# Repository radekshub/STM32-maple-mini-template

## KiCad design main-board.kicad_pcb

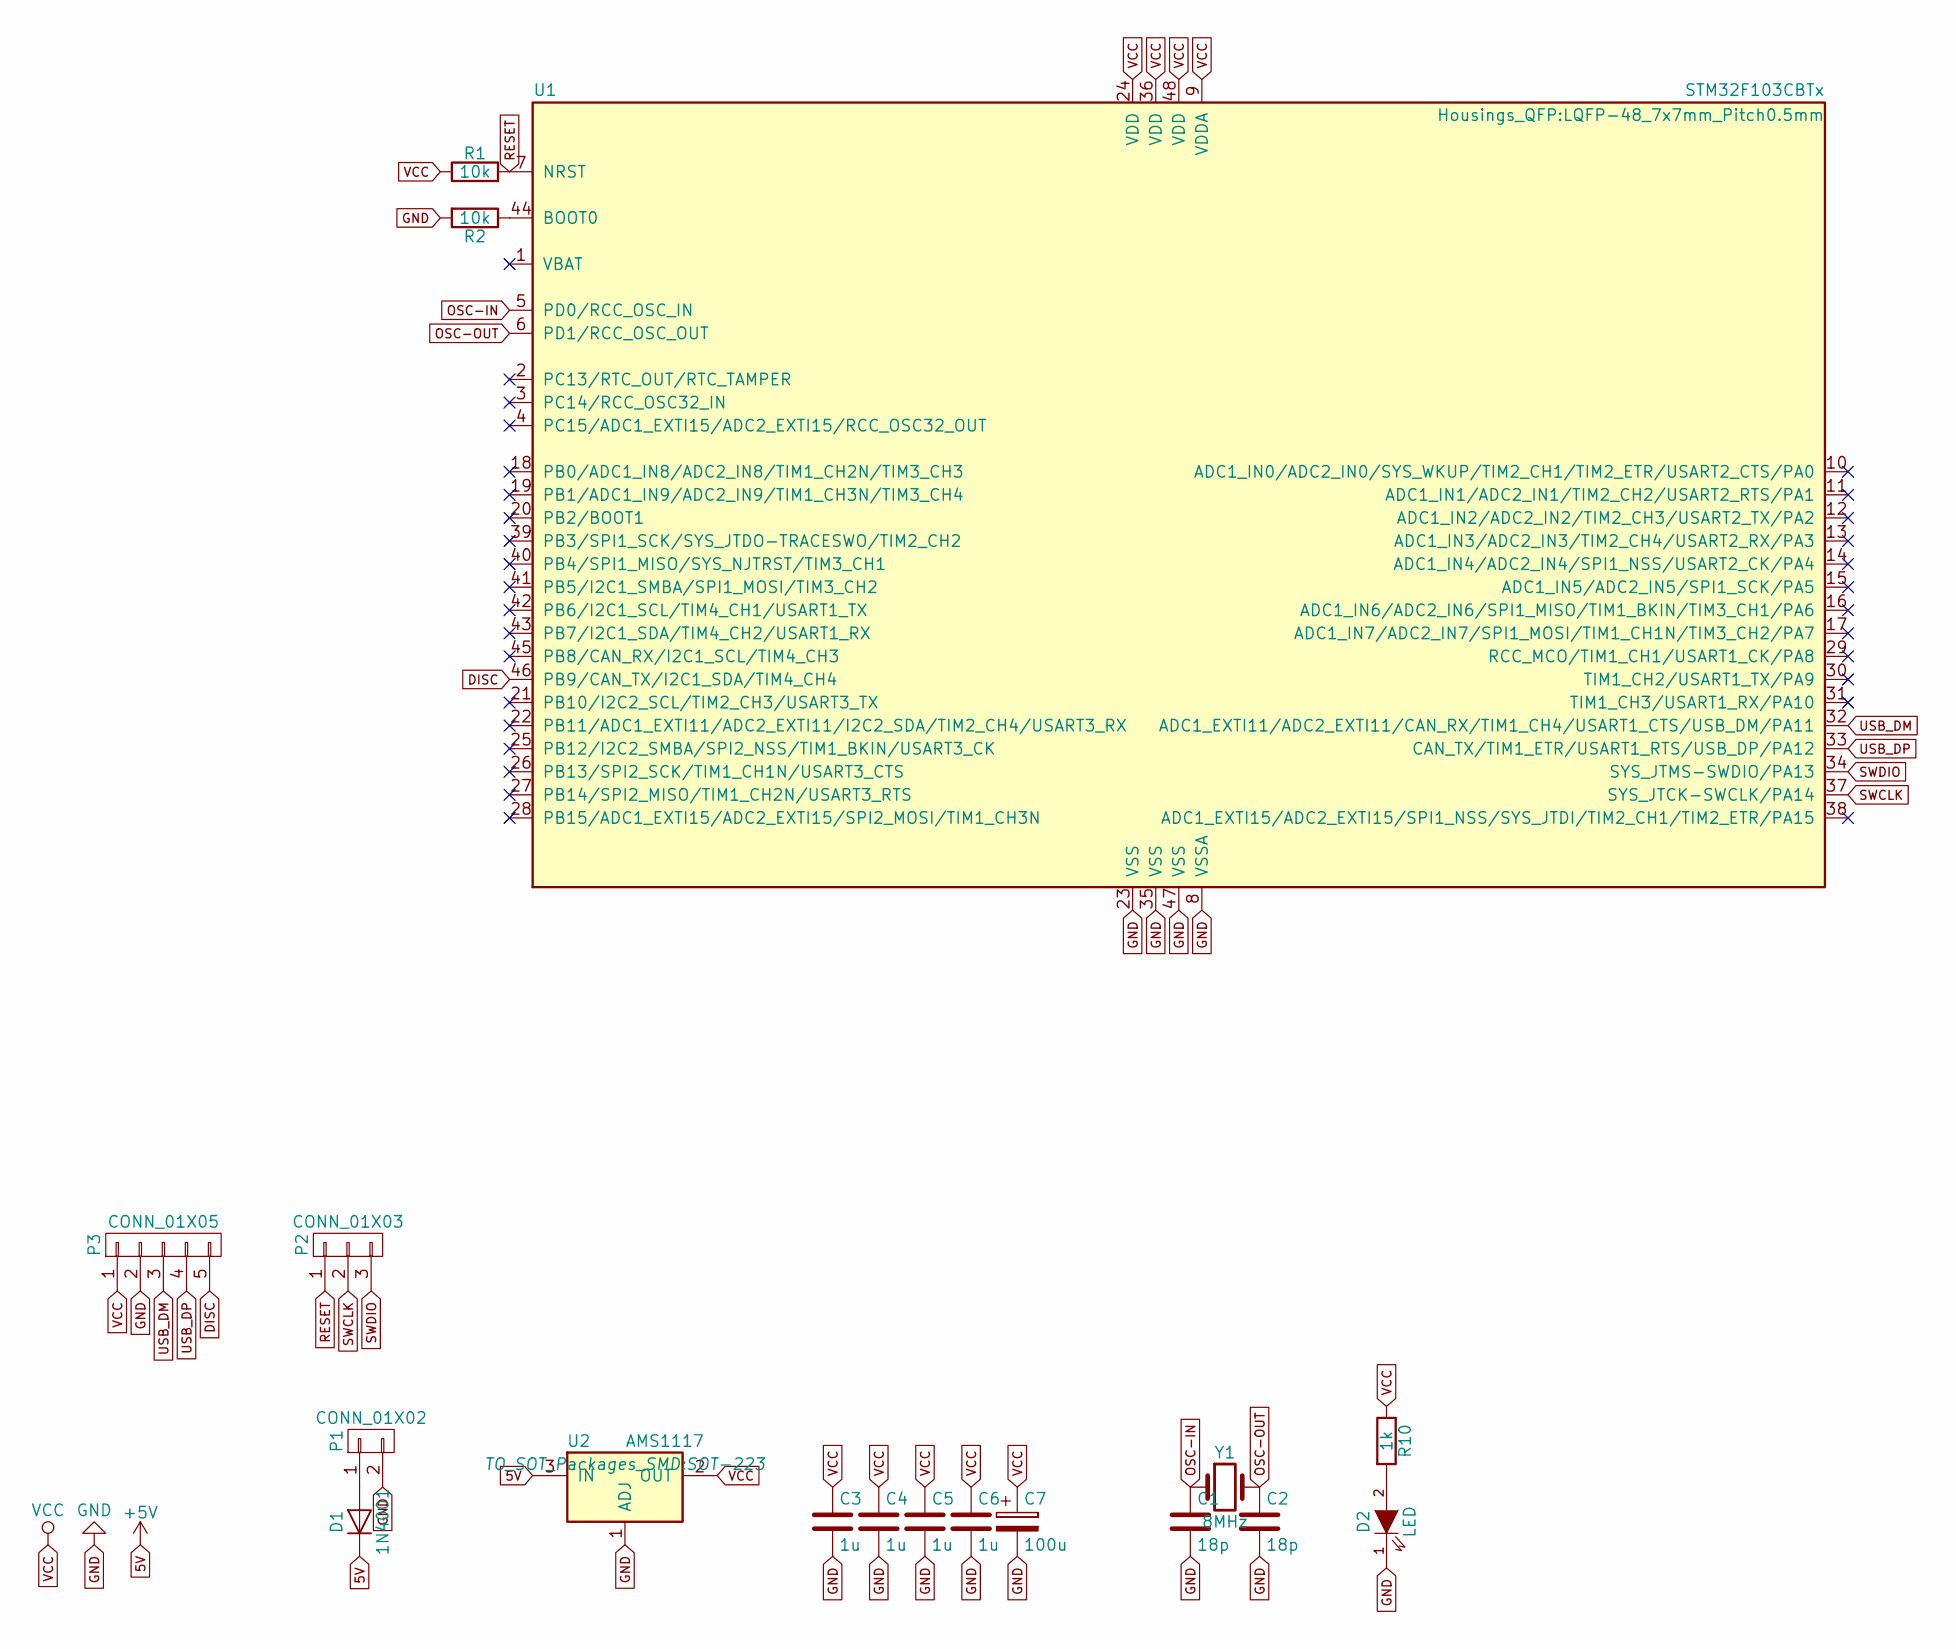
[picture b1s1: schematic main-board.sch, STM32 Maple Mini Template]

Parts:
C1, C2: 18p; C_0805
C3, C4, C5, C6: 1u; C_0805
C7: 100u; SMD-1210_Pol
D1: 1N4001; SMA_Standard
D2: LED; LED_0805
P1: CONN_01X02; Pin_Header_Straight_1x02
P2: CONN_01X03; Pin_Header_Straight_1x03
P3: CONN_01X05; Pin_Header_Straight_1x05
R1, R2: 10k; R_0805
R10: 1k; R_0805
U1: STM32F103CBTx; LQFP-48_7x7mm_Pitch0.5mm
U2: AMS1117; SOT-223
Y1: 8MHz; Crystal_HC49-U_Vertical

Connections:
5V: D1.1 (K), U2.3 (IN)
DISC: P3.5, U1.46 (PB9/CAN_TX/I2C1_SDA/TIM4_CH4)
GND: C1.2, C2.2, C3.2, C4.2, C5.2, C6.2, C7.2, D2.1 (K), P1.2, P3.2, R2.2, U1.8 (VSSA), U1.23 (VSS), U1.35 (VSS), U1.47 (VSS), U2.1 (ADJ)
unnamed: D1.2 (A), P1.1
unnamed: D2.2 (A), R10.2
unnamed: R2.1, U1.44 (BOOT0)
OSC-IN: C1.1, U1.5 (PD0/RCC_OSC_IN), Y1.1
OSC-OUT: C2.1, U1.6 (PD1/RCC_OSC_OUT), Y1.2
RESET: P2.1, R1.2, U1.7 (NRST)
SWCLK: P2.2, U1.37 (SYS_JTCK-SWCLK/PA14)
SWDIO: P2.3, U1.34 (SYS_JTMS-SWDIO/PA13)
USB_DM: P3.3, U1.32 (ADC1_EXTI11/ADC2_EXTI11/CAN_RX/TIM1_CH4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)
USB_DP: P3.4, U1.33 (CAN_TX/TIM1_ETR/USART1_RTS/USB_DP/PA12)
VCC: C3.1, C4.1, C5.1, C6.1, C7.1, P3.1, R1.1, R10.1, U1.9 (VDDA), U1.24 (VDD), U1.36 (VDD), U1.48 (VDD), U2.2 (OUT)

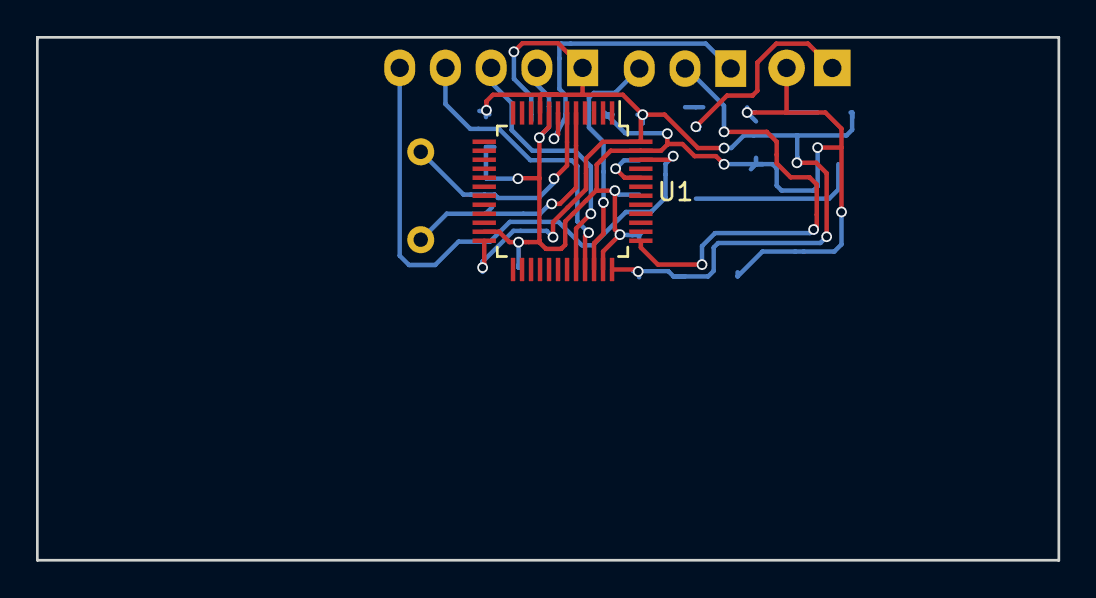
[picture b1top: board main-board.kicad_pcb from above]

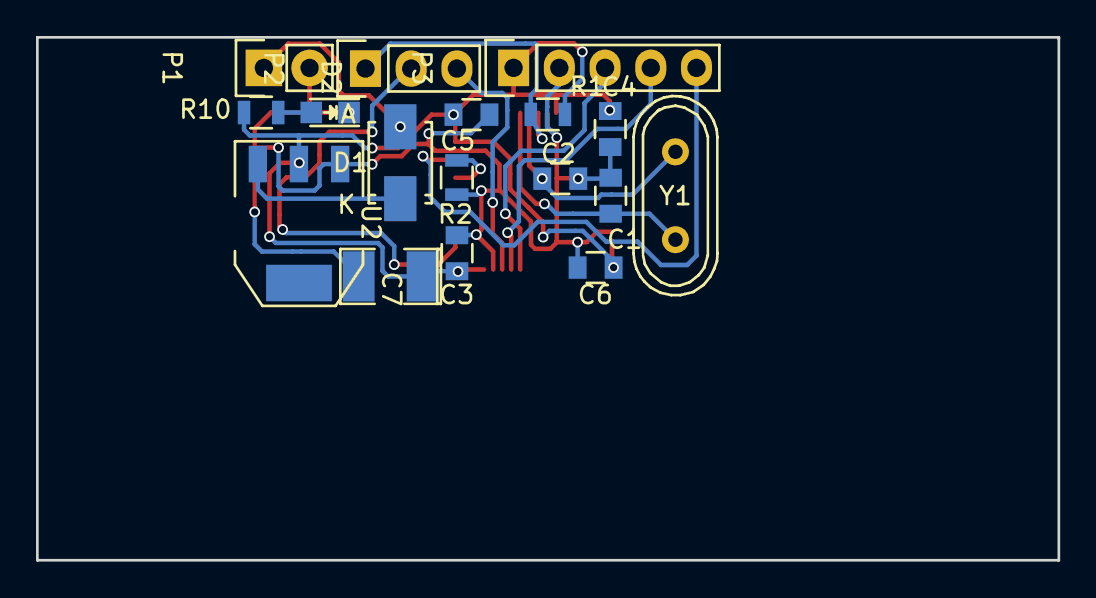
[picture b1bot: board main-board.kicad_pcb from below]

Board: 2 copper layers, 56.8 x 29.1 mm, 18 parts (17 on the bottom side), 14 nets.

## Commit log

2019-01-19 Added files to repository.
2019-01-19 Added Original Maple Mini Schematic Sheet.
2019-01-19 Added how to do fabrication procedure.
2019-01-19 Added 3D visualizations.
